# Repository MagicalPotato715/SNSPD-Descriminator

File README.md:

IMPORTANT INFO:
-
- CTD is the Constant Threshold Discriminator, and contains two amplifiers and one comparator.
- Compute contains a Teensy 4.1 MCU (for counting and general control purposes) and DAC60501MDGSR DAC for CTD reference voltage.
- The single board with both CTD and compute, while possible to manufacture, is not recommended due to general price spiking over 10x10cm
- There may be slight physical mismatches between corresponding parts on CTD/compute and the single board.
- PCBA Essentials should be enough for ordering PCBA; the BOM sources from Mouser; however, most, if not all, components can be found on Digikey.
- When ordering PCBA for the compute board, make sure to separately order Teensy 4.1 boards with header pins already attached (or attach them yourself).
- 

Logistics:
- 
- ***Compute DAC may not Function Correctly***: In this case, J8 (bottom left corner) is hardware controlled through a voltage divider and the 200 ohm trim.
- ***Scalability***: Although the current compute board only features 6 JST conns, the Teensy 4.1 allows this to be expandable to ~30.
- ***CTD Hardware Troubleshooting***: The two LEDs should both light if both 3.3v and 5v respectively, are active. The test points can be used to troubleshoot signals.
- ***Ratbites on Single Board Not Snapping***: There is a chance for the ratbites to not work; the board still functions without the connection severed.
- ***Simulation***: The SPICE models in the single board folder should be enough to simulate; the models may be slightly outdated, look in "Misc files" if needed.
- ***Required Electronics***: The CTD requires a biased SNSPD pulse input via the correct coaxial cable; CTD and compute need to be connected by a 1x5 male-male JST wire with 2.5mm pitch; the compute board requires an external stable 5v source via coaxial cable; the CTD cannot function without 5v coaxial cable power.

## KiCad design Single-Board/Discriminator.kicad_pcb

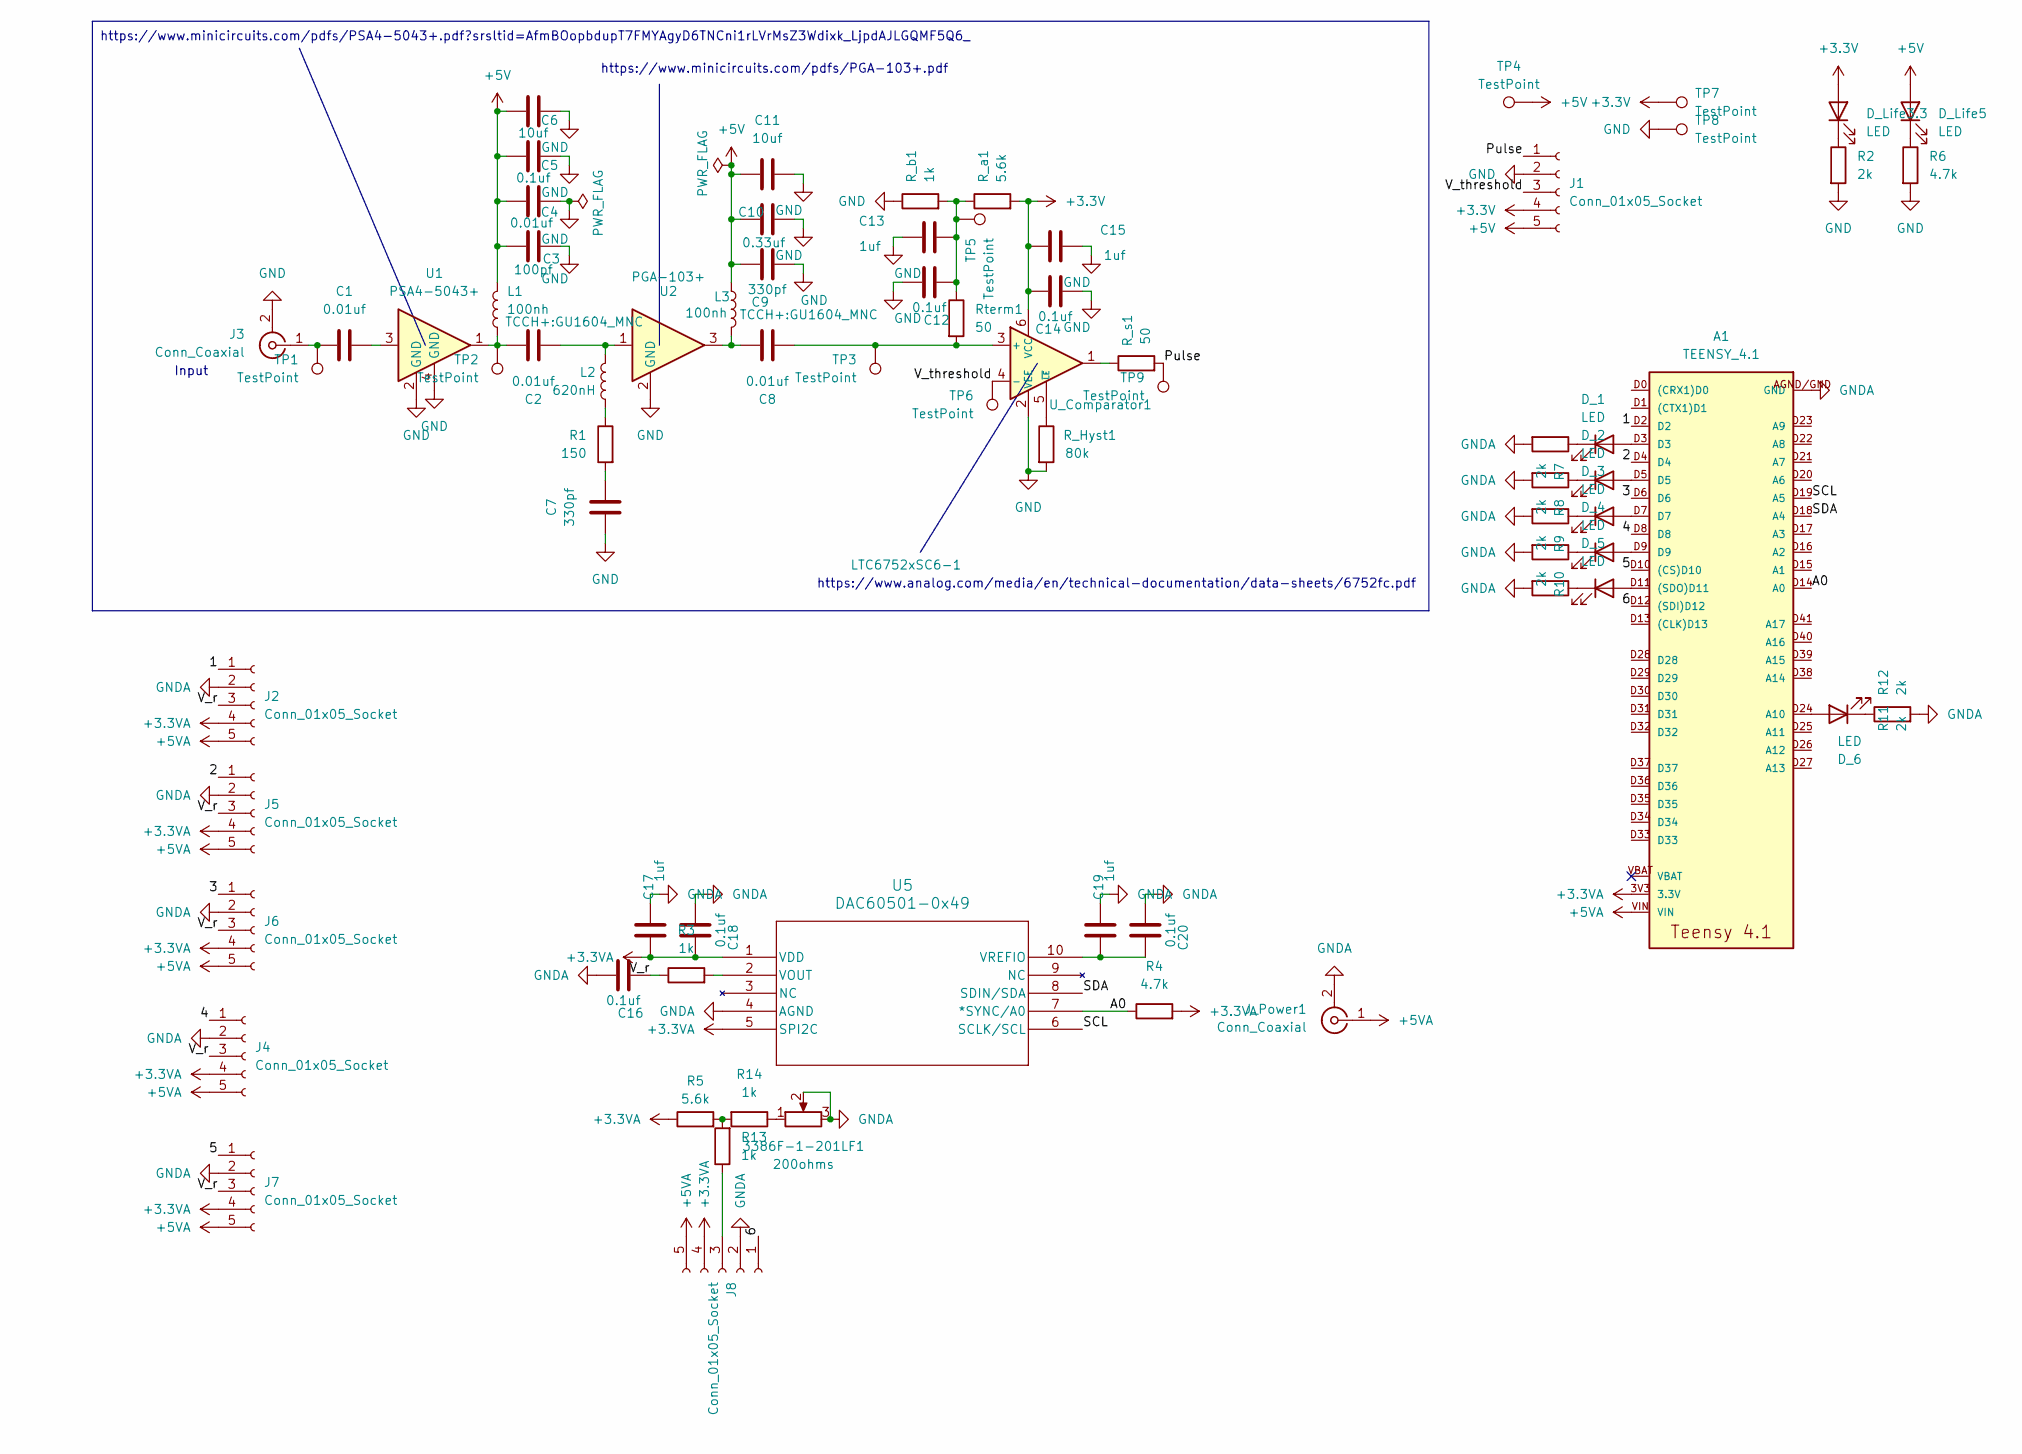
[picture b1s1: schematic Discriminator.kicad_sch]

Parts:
3386F-1-201LF1: 200ohms; Potentiometer_Bourns_3386F_Vertical
A1: TEENSY_4.1; TEENSY_LONG_EXT
C1, C2, C4, C8: 0.01uf; C_0402_1005Metric
C3: 100pf; C_0402_1005Metric
C5, C12, C14, C16, C18, C20: 0.1uf; C_0603_1608Metric
C6, C11: 10uf; C_0805_2012Metric
C7: 330pf; C_0603_1608Metric
C9: 330pf; C_0402_1005Metric
C10: 0.33uf; C_0603_1608Metric
C13, C15, C17, C19: 1uf; C_0603_1608Metric
D_1, D_2, D_3, D_4, D_5, D_6: LED; LED_0603_1608Metric
D_Life3.3, D_Life5: LED; LED_0603_1608Metric
J1, J2, J4, J5, J6, J7, J8: Conn_01x05_Socket; JST_XH_B5B-XH-A_1x05_P2.50mm_Vertical
J3: Conn_Coaxial; SMA_Samtec_SMA-J-P-H-ST-EM1_EdgeMount
J_Power1: Conn_Coaxial; SMA_Samtec_SMA-J-P-H-ST-EM1_EdgeMount
L1, L3: 100nh; GU1604_MNC
L2: 620nH; L_0603_1608Metric
R1: 150; R_0603_1608Metric
R2, R7, R8, R9, R10, R11, R12: 2k; R_0603_1608Metric
R3, R13, R14: 1k; R_0603_1608Metric
R4, R6: 4.7k; R_0603_1608Metric
R5: 5.6k; R_0603_1608Metric
R_Hyst1: 80k; R_0603_1608Metric
R_a1: 5.6k; R_0603_1608Metric
R_b1: 1k; R_0603_1608Metric
R_s1: 50; R_0402_1005Metric
Rterm1: 50; R_0402_1005Metric
TP1, TP2, TP3, TP4, TP5, TP6, TP7, TP8, TP9: TestPoint; TestPoint_Pad_1.0x1.0mm
U1: PSA4-5043+; MMM1362_MNC
U2: PGA-103+; SOT-89-3
U5: DAC60501-0x49; DGS10_TEX
U_Comparator1: LTC6752xSC6-1; SOT-363_SC-70-6

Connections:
+3.3V: C14.1, C15.1, D_Life3.3.2 (A), J1.4, R_a1.2, TP7.1, U_Comparator1.6 (VCC)
+3.3VA: A1.3V3 (3.3V), A1.3V3@2 (3.3V), A1.3V3@3 (3.3V), C17.1, C18.1, J2.4, J4.4, J5.4, J6.4, J7.4, J8.4, R4.2, R5.1, U5.1 (VDD), U5.5 (SPI2C)
+5V: C3.1, C4.1, C5.1, C6.1, C9.1, C10.1, C11.1, D_Life5.2 (A), J1.5, L1.3, L3.3, TP4.1
+5VA: A1.VIN, J2.5, J4.5, J5.5, J6.5, J7.5, J8.5, J_Power1.1 (In)
/1: A1.D2, J2.1
/2: A1.D4, J5.1
/3: A1.D6, J6.1
/4: A1.D8, J4.1
/5: A1.D10 ((CS)D10), J7.1
/6: A1.D12 ((SDI)D12), J8.1
/A0: A1.D14 (A0), R4.1, U5.7 (*SYNC/A0)
/Pulse: J1.1, R_s1.2, TP9.1
/SCL: A1.D19 (A5), U5.6 (SCLK/SCL)
/SDA: A1.D18 (A4), U5.8 (SDIN/SDA)
/V_r: C16.1, J2.3, J4.3, J5.3, J6.3, J7.3, R3.1
/V_threshold: J1.3, TP6.1, U_Comparator1.4 (-)
GND: C3.2, C4.2, C5.2, C6.2, C7.2, C9.2, C10.2, C11.2, C12.2, C13.2, C14.2, C15.2, J1.2, J3.2 (Ext), R2.2, R6.2, R_Hyst1.2, R_b1.1, TP8.1, U1.2 (GND), U1.4 (GND), U2.2 (GND), U_Comparator1.2 (VEE)
GNDA: 3386F-1-201LF1.2, 3386F-1-201LF1.3, A1.AGND/GND (GND), A1.GND, A1.GND@2 (GND), C16.2, C17.2, C18.2, C19.2, C20.2, J2.2, J4.2, J5.2, J6.2, J7.2, J8.2, J_Power1.2 (Ext), R7.2, R8.2, R9.2, R10.2, R11.2, R12.2, U5.4 (AGND)
unnamed: 3386F-1-201LF1.1, R14.1
unnamed: A1.D11 ((SDO)D11), D_5.2 (A)
unnamed: A1.D24 (A10), D_6.2 (A)
unnamed: C1.1, U1.3
unnamed: C2.1, L2.1, U2.1
unnamed: C2.2, L1.1, TP2.1, U1.1
unnamed: C7.1, R1.2
unnamed: C8.1, L3.1, U2.3
unnamed: C12.1, C13.1, R_a1.1, R_b1.2, Rterm1.1, TP5.1
unnamed: A1.D3, D_1.2 (A)
unnamed: D_1.1 (K), R7.1
unnamed: A1.D5, D_2.2 (A)
unnamed: D_2.1 (K), R8.1
unnamed: A1.D7, D_3.2 (A)
unnamed: D_3.1 (K), R9.1
unnamed: A1.D9, D_4.2 (A)
unnamed: D_4.1 (K), R10.1
unnamed: D_5.1 (K), R11.1
unnamed: D_6.1 (K), R12.1
unnamed: D_Life3.3.1 (K), R2.1
unnamed: D_Life5.1 (K), R6.1
unnamed: C1.2, J3.1 (In), TP1.1
unnamed: J8.3, R13.1
unnamed: L2.2, R1.1
unnamed: R5.2, R13.2, R14.2
unnamed: R_s1.1, U_Comparator1.1
unnamed: R3.2, U5.2 (VOUT)
unnamed: C19.1, C20.1, U5.10 (VREFIO)
unnamed: C8.2, Rterm1.2, TP3.1, U_Comparator1.3 (+)
unnamed: R_Hyst1.1, U_Comparator1.5 (~LE)

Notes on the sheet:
https://www.minicircuits.com/pdfs/PSA4-5043+.pdf?srsltid=AfmBOopbdupT7FMYAgyD6TNCni1rLVrMsZ3Wdixk_LjpdAJLGQMF5Q6_
Input
https://www.minicircuits.com/pdfs/PGA-103+.pdf
https://www.analog.com/media/en/technical-documentation/data-sheets/6752fc.pdf

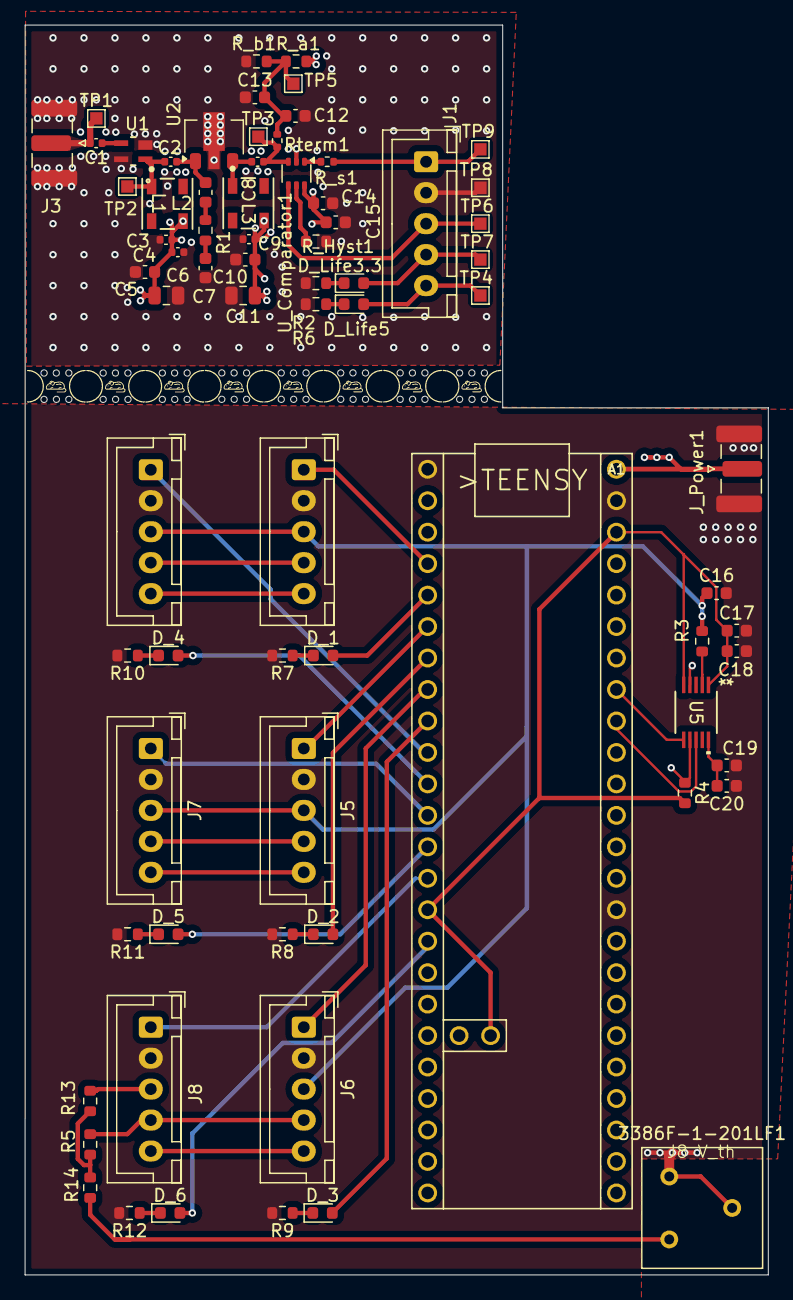
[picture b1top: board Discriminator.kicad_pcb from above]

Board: 4 copper layers, 60.0 x 100.9 mm, 82 parts (0 on the bottom side), 48 nets.

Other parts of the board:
mouse-bite-2.54mm-4.66mm, mouse-bite-2.54mm-4.66mm#2, mouse-bite-2.54mm-4.66mm#3, mouse-bite-2.54mm-4.66mm#4, mouse-bite-2.54mm-4.66mm#5, mouse-bite-2.54mm-4.66mm#6, mouse-bite-2.54mm-4.66mm#7, mouse-bite-2.54mm-4.66mm#8: VAL**; mouse-bite-2.54mm-4.66mm

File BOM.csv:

"Id";"Designator";"Footprint";"Quantity";"Designation";"Supplier and ref";
1;"RM-065-201";"Potentiometer_Runtron_RM-065_Vertical";1;"200ohms";;;
2;"R14,R13,R3,R_b1";"R_0603_1608Metric";4;"1k";;;
3;"R5,R_a1";"R_0603_1608Metric";2;"5.6k";;;
4;"C20,C18,C16,C14,C12,C5";"C_0603_1608Metric";6;"0.1uf";;;
5;"D_1,D_2,D_3,D_4,D_5,D_6,D_Life3.3,D_Life5";"LED_0603_1608Metric";8;"LED";;;
6;"C17,C19,C15,C13";"C_0603_1608Metric";4;"1uf";;;
7;"J2,J4,J5,J6,J7,J8,J1";"JST_XH_B5B-XH-A_1x05_P2.50mm_Vertical";7;"Conn_01x05_Socket";;;
8;"J_Power1,J3";"SMA_Samtec_SMA-J-P-H-ST-EM1_EdgeMount";2;"Conn_Coaxial";;;
9;"A1";"TEENSY_LONG_EXT";1;"TEENSY_4.1";;;
10;"R7,R8,R9,R10,R11,R12,R2";"C_0603_1608Metric";7;"2k";;;
11;"U5";"DGS10_TEX";1;"DAC60501-0x49";;;
12;"R4";"R_0603_1608Metric";1;"4.7k";;;
13;"mouse-bite-2.54mm-4.66mm,mouse-bite-2.54mm-4.66mm,mouse-bite-2.54mm-4.66mm,mouse-bite-2.54mm-4.66mm,mouse-bite-2.54mm-4.66mm,mouse-bite-2.54mm-4.66mm,mouse-bite-2.54mm-4.66mm,mouse-bite-2.54mm-4.66mm";"mouse-bite-2.54mm-4.66mm";8;"VAL**";;;
14;"TP9,TP8,TP7,TP6,TP5,TP4,TP3,TP2,TP1";"TestPoint_Pad_1.0x1.0mm";9;"TestPoint";;;
15;"R6";"C_0603_1608Metric";1;"4.7k";;;
16;"U_Comparator1";"SOT-363_SC-70-6";1;"LTC6752xSC6-1";;;
17;"L2";"L_0603_1608Metric";1;"620nH";;;
18;"C9";"C_0402_1005Metric";1;"330pf";;;
19;"L1,L3";"GU1604_MNC";2;"L";;;
20;"C2,C1,C8,C4";"C_0402_1005Metric";4;"0.01uf";;;
21;"U1";"MMM1362_MNC";1;"PSA4-5043+";;;
22;"U2";"SOT-89-3";1;"PGA-103+";;;
23;"R_s1,Rterm1";"R_0402_1005Metric";2;"50";;;
24;"R_Hyst1";"R_0603_1608Metric";1;"80k";;;
25;"R1";"R_0603_1608Metric";1;"150";;;
26;"C11,C6";"C_0805_2012Metric";2;"10uf";;;
27;"C10";"C_0603_1608Metric";1;"0.33uf";;;
28;"C7";"C_0603_1608Metric";1;"330pf";;;
29;"C3";"C_0402_1005Metric";1;"100pf";;;
